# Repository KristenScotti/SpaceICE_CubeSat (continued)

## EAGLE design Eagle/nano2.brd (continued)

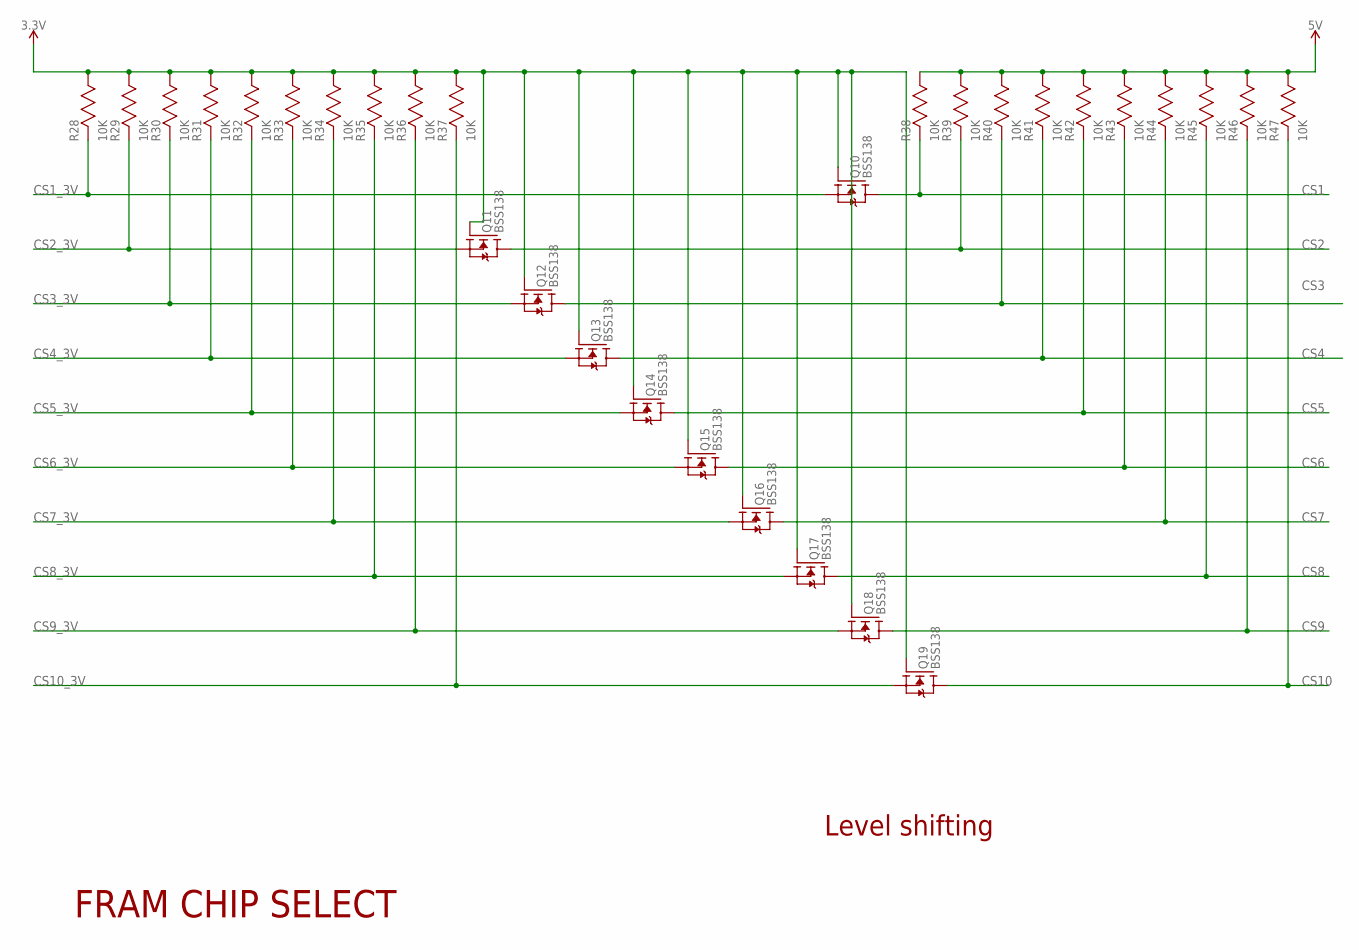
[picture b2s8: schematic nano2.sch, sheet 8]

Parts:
Q10, Q11, Q12, Q13, Q14, Q15, Q16, Q17, Q18, Q19: BSS138; SOT-23
R28, R29, R30, R31, R32, R33, R34, R35, R36, R37, R38, R39, R40, R41, R42, R43, R44, R45, R46, R47: 10K; RC0603N

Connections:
3.3V: Q10.G, Q11.G, Q12.G, Q13.G, Q14.G, Q15.G, Q16.G, Q17.G, Q18.G, Q19.G, R28.1 (11), R29.1 (11), R30.1 (11), R31.1 (11), R32.1 (11), R33.1 (11), R34.1 (11), R35.1 (11), R36.1 (11), R37.1 (11); also elsewhere on the board
5V: R38.1 (11), R39.1 (11), R40.1 (11), R41.1 (11), R42.1 (11), R43.1 (11), R44.1 (11), R45.1 (11), R46.1 (11), R47.1 (11); also elsewhere on the board
CS1: Q10.D, R38.2 (22); also elsewhere on the board
CS1_3V: Q10.S, R28.2 (22); also elsewhere on the board
CS2: Q11.D, R39.2 (22); also elsewhere on the board
CS2_3V: Q11.S, R29.2 (22); also elsewhere on the board
CS3: Q12.D, R40.2 (22); also elsewhere on the board
CS3_3V: Q12.S, R30.2 (22); also elsewhere on the board
CS4: Q13.D, R41.2 (22); also elsewhere on the board
CS4_3V: Q13.S, R31.2 (22); also elsewhere on the board
CS5: Q14.D, R42.2 (22); also elsewhere on the board
CS5_3V: Q14.S, R32.2 (22); also elsewhere on the board
CS6: Q15.D, R43.2 (22); also elsewhere on the board
CS6_3V: Q15.S, R33.2 (22); also elsewhere on the board
CS7: Q16.D, R44.2 (22); also elsewhere on the board
CS7_3V: Q16.S, R34.2 (22); also elsewhere on the board
CS8: Q17.D, R45.2 (22); also elsewhere on the board
CS8_3V: Q17.S, R35.2 (22); also elsewhere on the board
CS9: Q18.D, R46.2 (22); also elsewhere on the board
CS9_3V: Q18.S, R36.2 (22); also elsewhere on the board
CS10: Q19.D, R47.2 (22); also elsewhere on the board
CS10_3V: Q19.S, R37.2 (22); also elsewhere on the board

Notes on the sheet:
Level shifting
FRAM CHIP SELECT

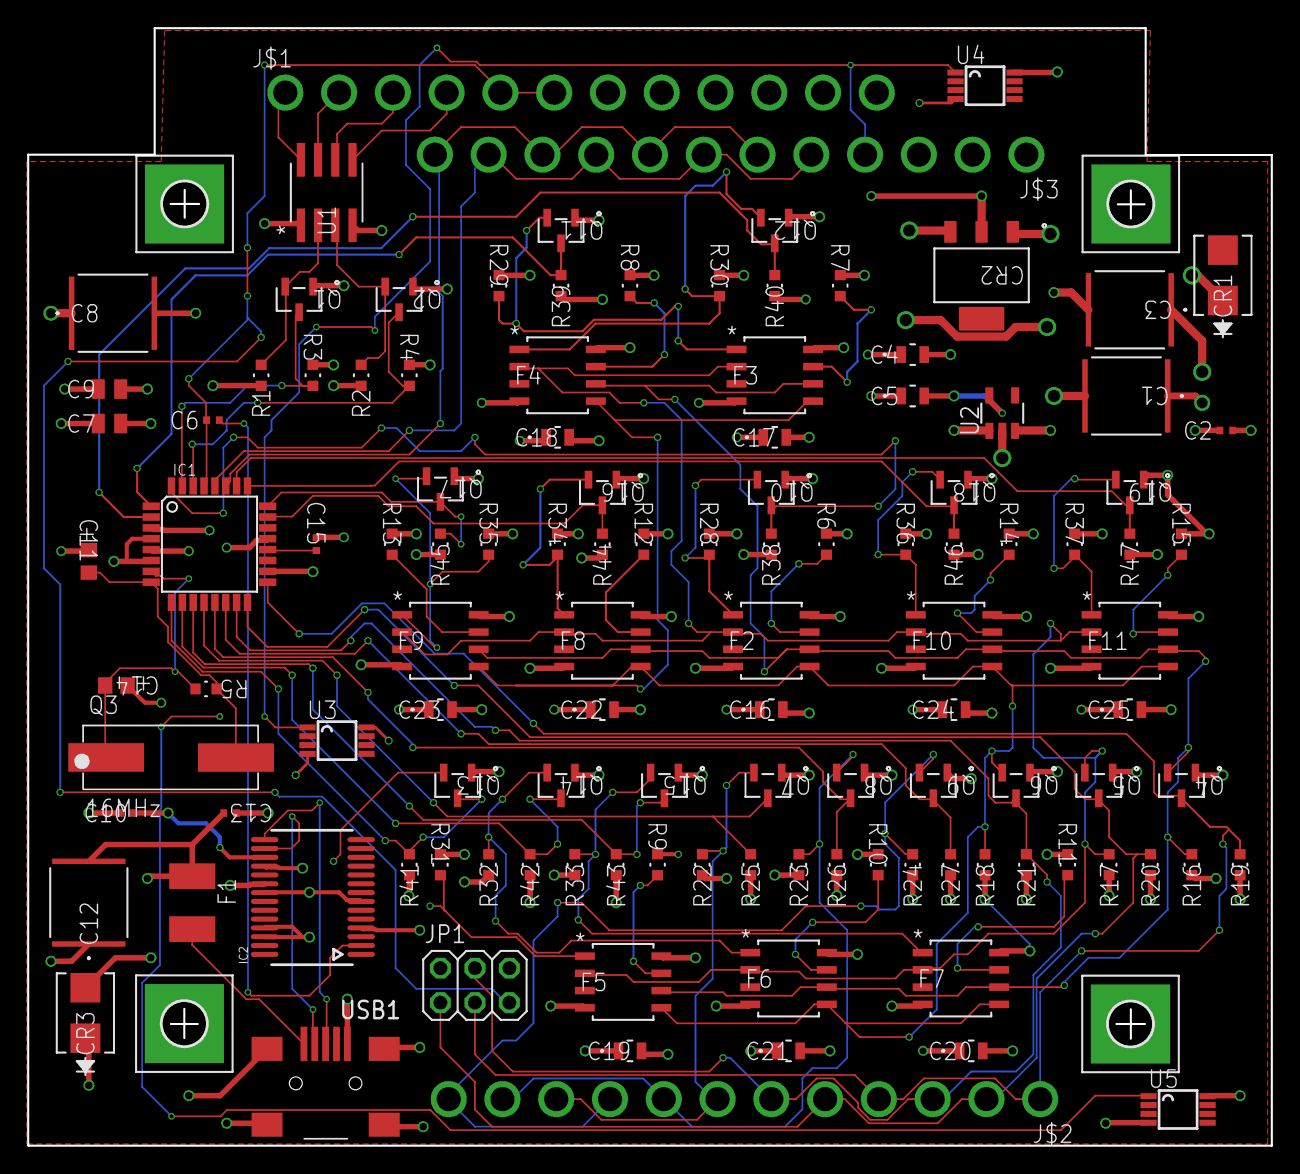
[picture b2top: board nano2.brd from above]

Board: 4 copper layers, 91.6 x 82.3 mm, 121 parts (0 on the bottom side), 66 nets.

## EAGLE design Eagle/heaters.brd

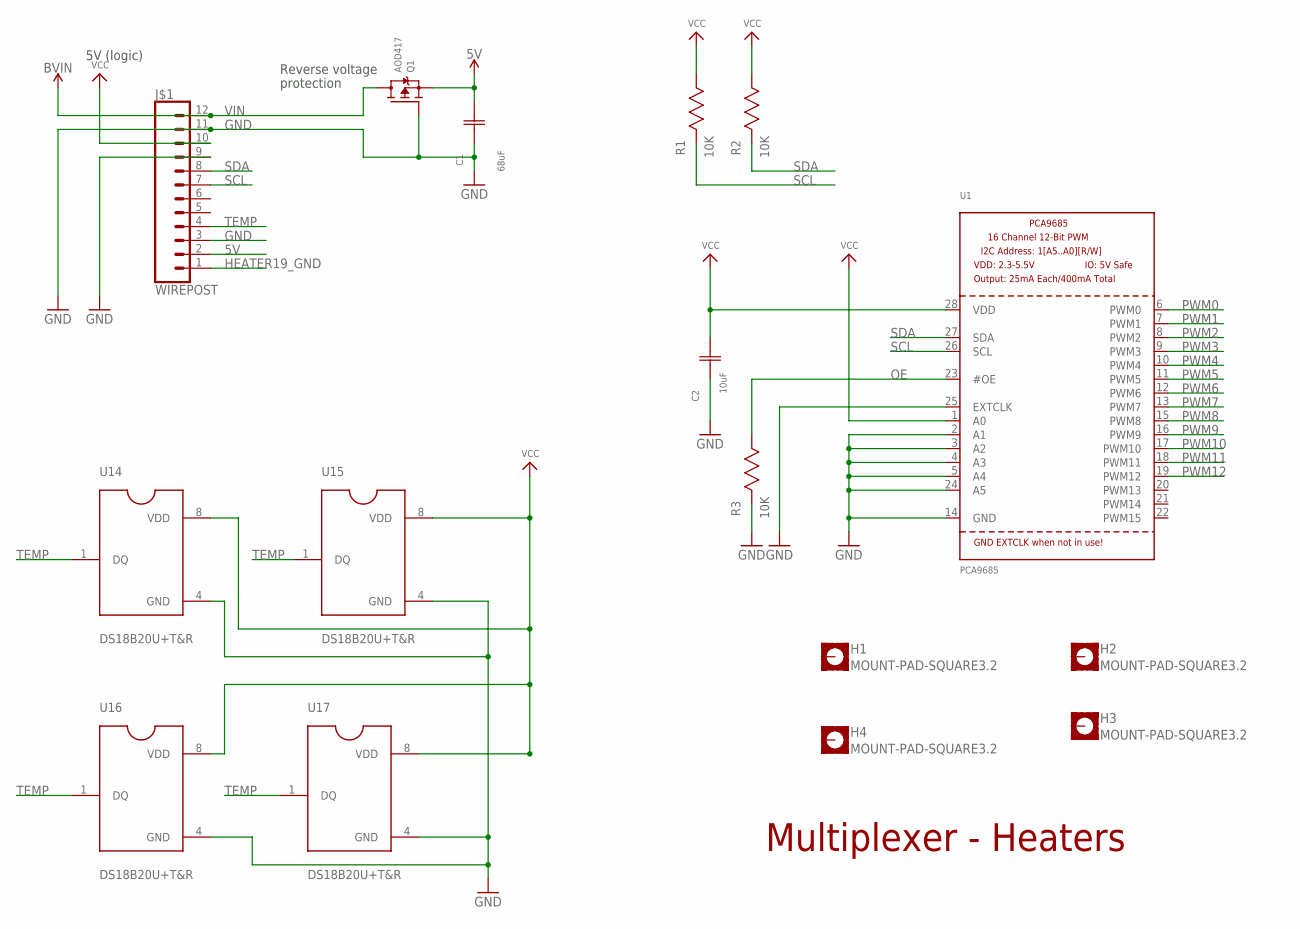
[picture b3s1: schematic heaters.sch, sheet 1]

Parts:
C1: 68uF; CAP_5750
C2: 10uF; 1206
H1, H2, H3, H4: MOUNT-PAD-SQUARE3.2; 3,2-PAD-SQUARE
J$1: WIREPOST; WIREWRAPPOST
Q1: AOD417; TO252
R1, R2, R3: 10K; RC0603N
U1: PCA9685; TSSOP28
U14, U15, U16, U17: DS18B20U+T&R; SOP65P500X110-8N

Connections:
5V: C1.2 (22), J$1.2, Q1.2 (S); also elsewhere on the board
GND: C1.1 (11), C2.1, J$1.3, J$1.9, J$1.11, Q1.1 (G), R3.2 (22), U1.2 (A1), U1.3 (A2), U1.4 (A3), U1.5 (A4), U1.14 (GND), U1.24 (A5), U1.25 (EXTCLK), U14.4 (GND), U15.4 (GND), U16.4 (GND), U17.4 (GND); also elsewhere on the board
HEATER19_GND: J$1.1
OE: R3.1 (11), U1.23 (#OE); also elsewhere on the board
PWM0: U1.6 (PWM0); also elsewhere on the board
PWM1: U1.7 (PWM1); also elsewhere on the board
PWM2: U1.8 (PWM2); also elsewhere on the board
PWM3: U1.9 (PWM3); also elsewhere on the board
PWM4: U1.10 (PWM4); also elsewhere on the board
PWM5: U1.11 (PWM5); also elsewhere on the board
PWM6: U1.12 (PWM6); also elsewhere on the board
PWM7: U1.13 (PWM7); also elsewhere on the board
PWM8: U1.15 (PWM8); also elsewhere on the board
PWM9: U1.16 (PWM9); also elsewhere on the board
PWM10: U1.17 (PWM10); also elsewhere on the board
PWM11: U1.18 (PWM11); also elsewhere on the board
PWM12: U1.19 (PWM12)
SCL: J$1.7, R1.2 (22), U1.26 (SCL); also elsewhere on the board
SDA: J$1.8, R2.2 (22), U1.27 (SDA); also elsewhere on the board
TEMP: J$1.4, U14.1 (DQ), U15.1 (DQ), U16.1 (DQ), U17.1 (DQ)
VCC: C2.2, J$1.10, R1.1 (11), R2.1 (11), U1.1 (A0), U1.28 (VDD), U14.8 (VDD), U15.8 (VDD), U16.8 (VDD), U17.8 (VDD); also elsewhere on the board
VIN: J$1.12, Q1.3 (D)

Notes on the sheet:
Reverse voltage
protection
5V (logic)
Multiplexer - Heaters

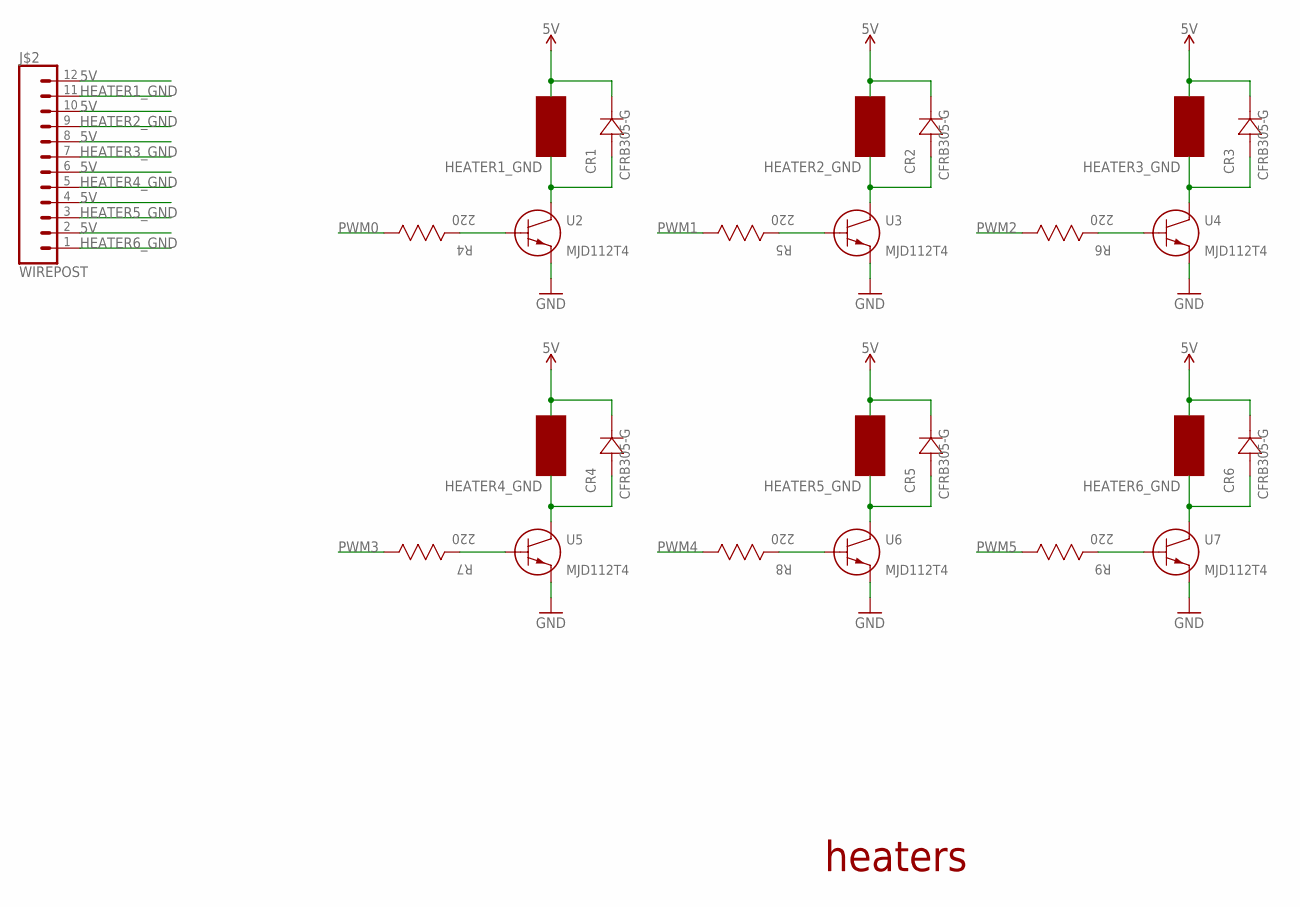
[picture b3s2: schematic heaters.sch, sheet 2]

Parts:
CR1, CR2, CR3, CR4, CR5, CR6: CFRB305-G; CFRB-G
J$2: WIREPOST; WIREWRAPPOST
R4, R5, R6, R7, R8, R9: 220; RC0603N
U2, U3, U4, U5, U6, U7: MJD112T4; DPAK

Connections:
5V: CR1.1 (2), CR2.1 (2), CR3.1 (2), CR4.1 (2), CR5.1 (2), CR6.1 (2), J$2.2, J$2.4, J$2.6, J$2.8, J$2.10, J$2.12; also elsewhere on the board
GND: U2.2 (E2), U3.2 (E2), U4.2 (E2), U5.2 (E2), U6.2 (E2), U7.2 (E2); also elsewhere on the board
HEATER1_GND: CR1.2 (1), J$2.11, U2.3 (C3)
HEATER2_GND: CR2.2 (1), J$2.9, U3.3 (C3)
HEATER3_GND: CR3.2 (1), J$2.7, U4.3 (C3)
HEATER4_GND: CR4.2 (1), J$2.5, U5.3 (C3)
HEATER5_GND: CR5.2 (1), J$2.3, U6.3 (C3)
HEATER6_GND: CR6.2 (1), J$2.1, U7.3 (C3)
unnamed: R5.2 (22), U3.1 (B1)
unnamed: R6.2 (22), U4.1 (B1)
unnamed: R7.2 (22), U5.1 (B1)
unnamed: R8.2 (22), U6.1 (B1)
unnamed: R9.2 (22), U7.1 (B1)
unnamed: R4.2 (22), U2.1 (B1)
PWM0: R4.1 (11); also elsewhere on the board
PWM1: R5.1 (11); also elsewhere on the board
PWM2: R6.1 (11); also elsewhere on the board
PWM3: R7.1 (11); also elsewhere on the board
PWM4: R8.1 (11); also elsewhere on the board
PWM5: R9.1 (11); also elsewhere on the board

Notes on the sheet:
HEATER
heaters

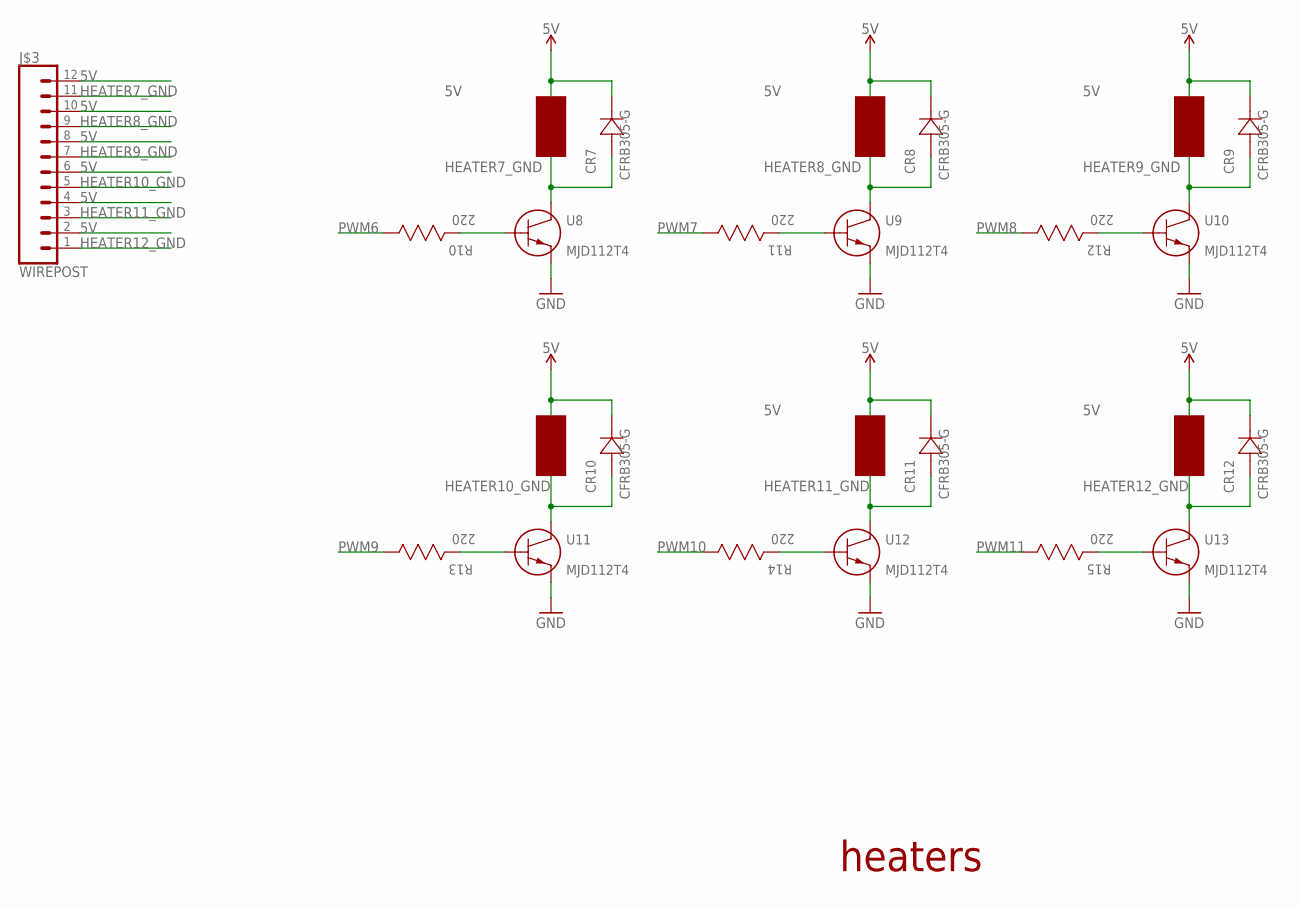
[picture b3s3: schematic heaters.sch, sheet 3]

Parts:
CR7, CR8, CR9, CR10, CR11, CR12: CFRB305-G; CFRB-G
J$3: WIREPOST; WIREWRAPPOST
R10, R11, R12, R13, R14, R15: 220; RC0603N
U8, U9, U10, U11, U12, U13: MJD112T4; DPAK

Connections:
5V: CR7.1 (2), CR8.1 (2), CR9.1 (2), CR10.1 (2), CR11.1 (2), CR12.1 (2), J$3.2, J$3.4, J$3.6, J$3.8, J$3.10, J$3.12; also elsewhere on the board
GND: U8.2 (E2), U9.2 (E2), U10.2 (E2), U11.2 (E2), U12.2 (E2), U13.2 (E2); also elsewhere on the board
HEATER7_GND: CR7.2 (1), J$3.11, U8.3 (C3)
HEATER8_GND: CR8.2 (1), J$3.9, U9.3 (C3)
HEATER9_GND: CR9.2 (1), J$3.7, U10.3 (C3)
HEATER10_GND: CR10.2 (1), J$3.5, U11.3 (C3)
HEATER11_GND: CR11.2 (1), J$3.3, U12.3 (C3)
HEATER12_GND: CR12.2 (1), J$3.1, U13.3 (C3)
unnamed: R10.2 (22), U8.1 (B1)
unnamed: R11.2 (22), U9.1 (B1)
unnamed: R12.2 (22), U10.1 (B1)
unnamed: R13.2 (22), U11.1 (B1)
unnamed: R14.2 (22), U12.1 (B1)
unnamed: R15.2 (22), U13.1 (B1)
PWM6: R10.1 (11); also elsewhere on the board
PWM7: R11.1 (11); also elsewhere on the board
PWM8: R12.1 (11); also elsewhere on the board
PWM9: R13.1 (11); also elsewhere on the board
PWM10: R14.1 (11); also elsewhere on the board
PWM11: R15.1 (11); also elsewhere on the board

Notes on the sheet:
HEATER
heaters

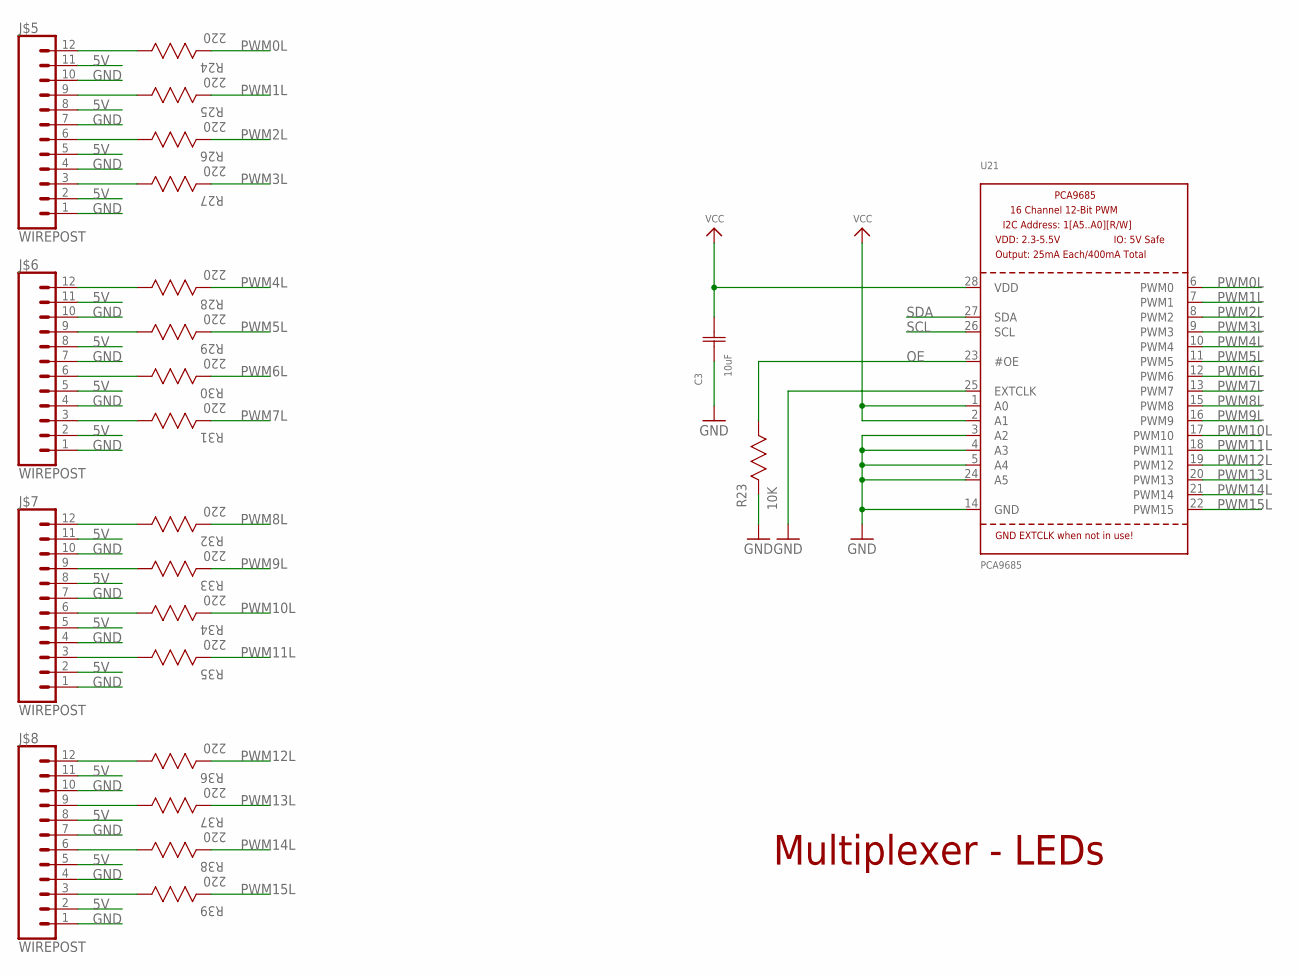
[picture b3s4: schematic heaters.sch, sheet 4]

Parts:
C3: 10uF; 1206
J$5, J$6, J$7, J$8: WIREPOST; WIREWRAPPOST
R23: 10K; RC0603N
R24, R25, R26, R27, R28, R29, R30, R31, R32, R33, R34, R35, R36, R37, R38, R39: 220; RC0603N
U21: PCA9685; TSSOP28

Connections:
5V: J$5.2, J$5.5, J$5.8, J$5.11, J$6.2, J$6.5, J$6.8, J$6.11, J$7.2, J$7.5, J$7.8, J$7.11, J$8.2, J$8.5, J$8.8, J$8.11; also elsewhere on the board
GND: C3.1, J$5.1, J$5.4, J$5.7, J$5.10, J$6.1, J$6.4, J$6.7, J$6.10, J$7.1, J$7.4, J$7.7, J$7.10, J$8.1, J$8.4, J$8.7, J$8.10, R23.2 (22), U21.3 (A2), U21.4 (A3), U21.5 (A4), U21.14 (GND), U21.24 (A5), U21.25 (EXTCLK); also elsewhere on the board
unnamed: J$5.12, R24.1 (11)
unnamed: J$5.9, R25.1 (11)
unnamed: J$5.6, R26.1 (11)
unnamed: J$5.3, R27.1 (11)
unnamed: J$6.12, R28.1 (11)
unnamed: J$6.9, R29.1 (11)
unnamed: J$6.6, R30.1 (11)
unnamed: J$6.3, R31.1 (11)
unnamed: J$7.12, R32.1 (11)
unnamed: J$7.9, R33.1 (11)
unnamed: J$7.6, R34.1 (11)
unnamed: J$7.3, R35.1 (11)
unnamed: J$8.12, R36.1 (11)
unnamed: J$8.9, R37.1 (11)
unnamed: J$8.6, R38.1 (11)
unnamed: J$8.3, R39.1 (11)
OE: R23.1 (11), U21.23 (#OE); also elsewhere on the board
PWM0L: R24.2 (22), U21.6 (PWM0)
PWM1L: R25.2 (22), U21.7 (PWM1)
PWM2L: R26.2 (22), U21.8 (PWM2)
PWM3L: R27.2 (22), U21.9 (PWM3)
PWM4L: R28.2 (22), U21.10 (PWM4)
PWM5L: R29.2 (22), U21.11 (PWM5)
PWM6L: R30.2 (22), U21.12 (PWM6)
PWM7L: R31.2 (22), U21.13 (PWM7)
PWM8L: R32.2 (22), U21.15 (PWM8)
PWM9L: R33.2 (22), U21.16 (PWM9)
PWM10L: R34.2 (22), U21.17 (PWM10)
PWM11L: R35.2 (22), U21.18 (PWM11)
PWM12L: R36.2 (22), U21.19 (PWM12)
PWM13L: R37.2 (22), U21.20 (PWM13)
PWM14L: R38.2 (22), U21.21 (PWM14)
PWM15L: R39.2 (22), U21.22 (PWM15)
SCL: U21.26 (SCL); also elsewhere on the board
SDA: U21.27 (SDA); also elsewhere on the board
VCC: C3.2, U21.1 (A0), U21.2 (A1), U21.28 (VDD); also elsewhere on the board

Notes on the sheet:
Multiplexer - LEDs

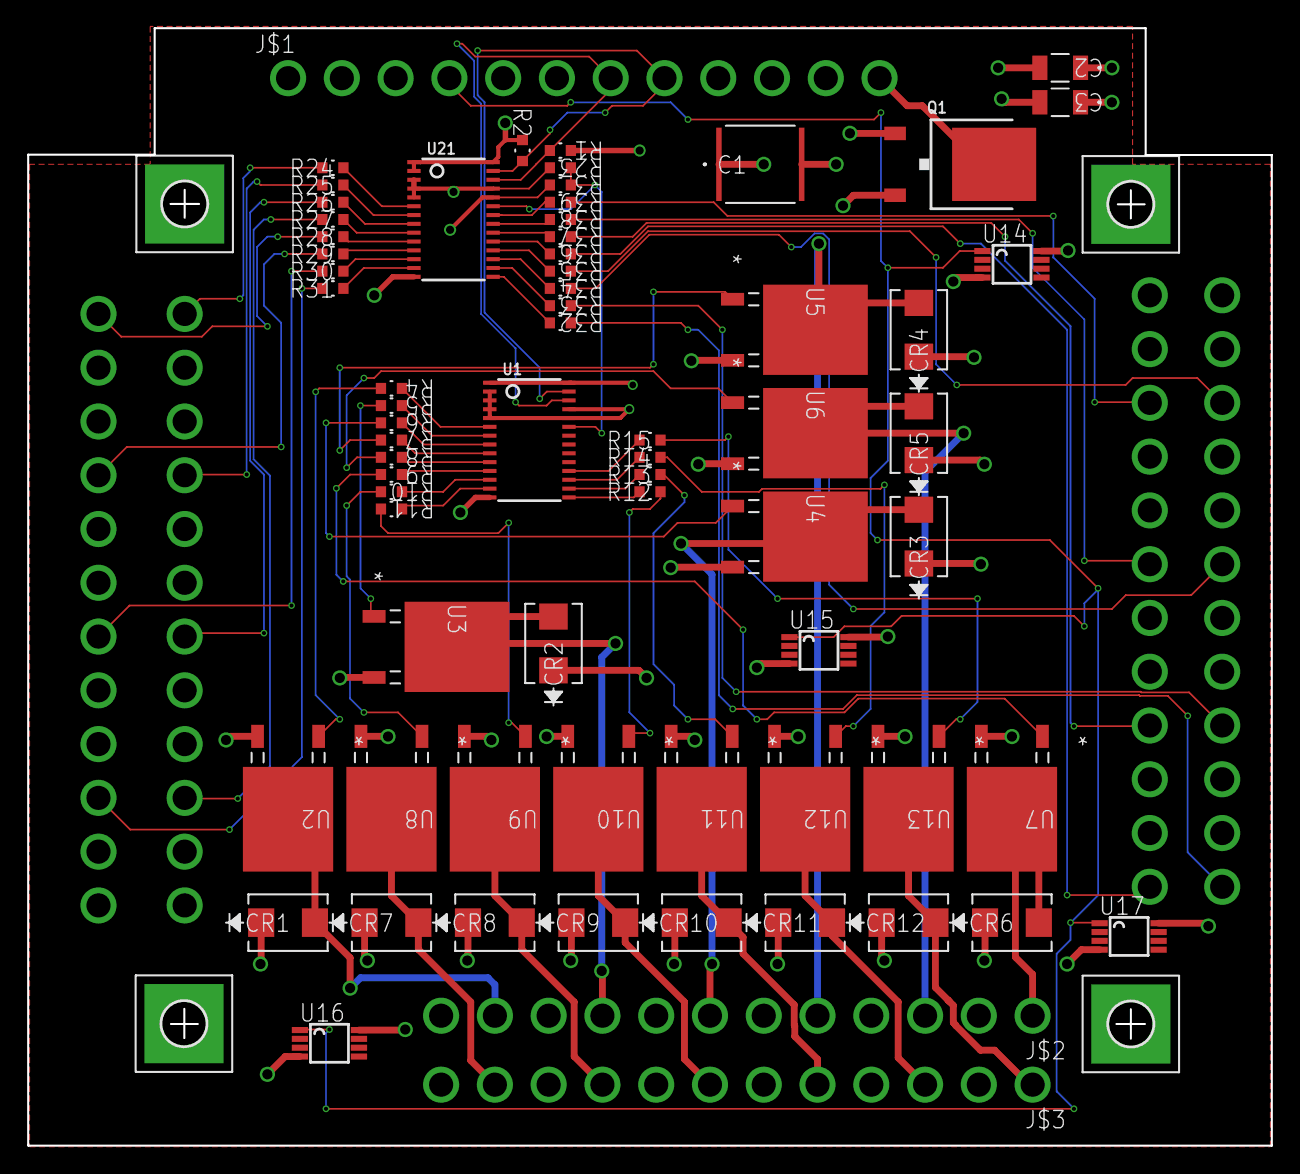
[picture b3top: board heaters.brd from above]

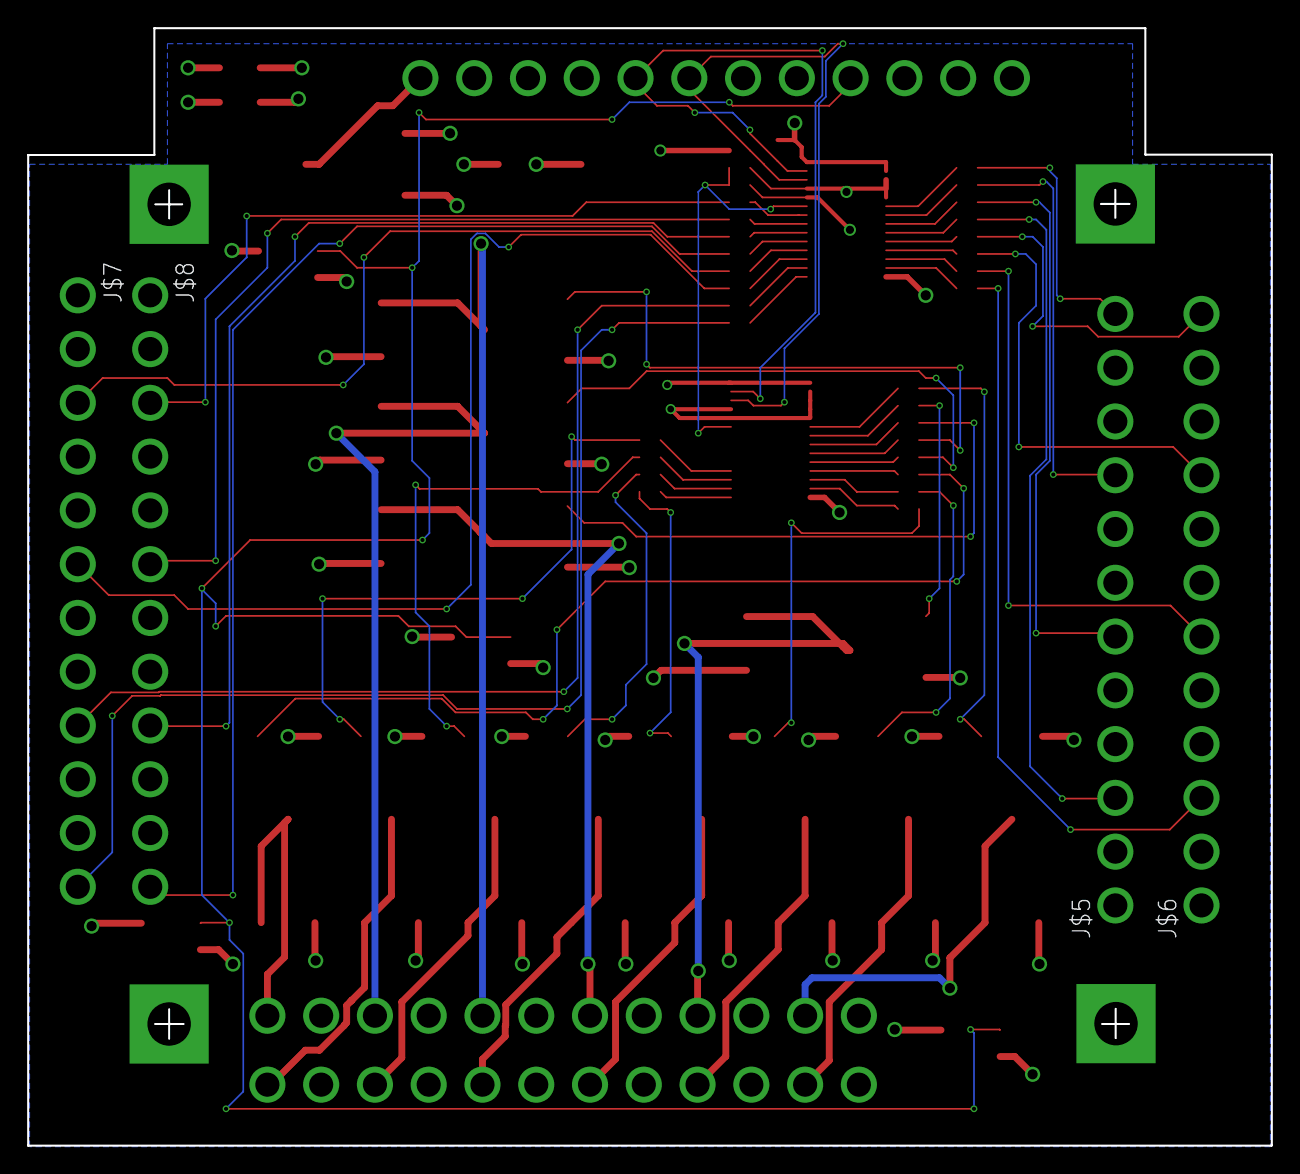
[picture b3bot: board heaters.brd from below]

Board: 4 copper layers, 91.6 x 82.3 mm, 77 parts (4 on the bottom side), 76 nets.

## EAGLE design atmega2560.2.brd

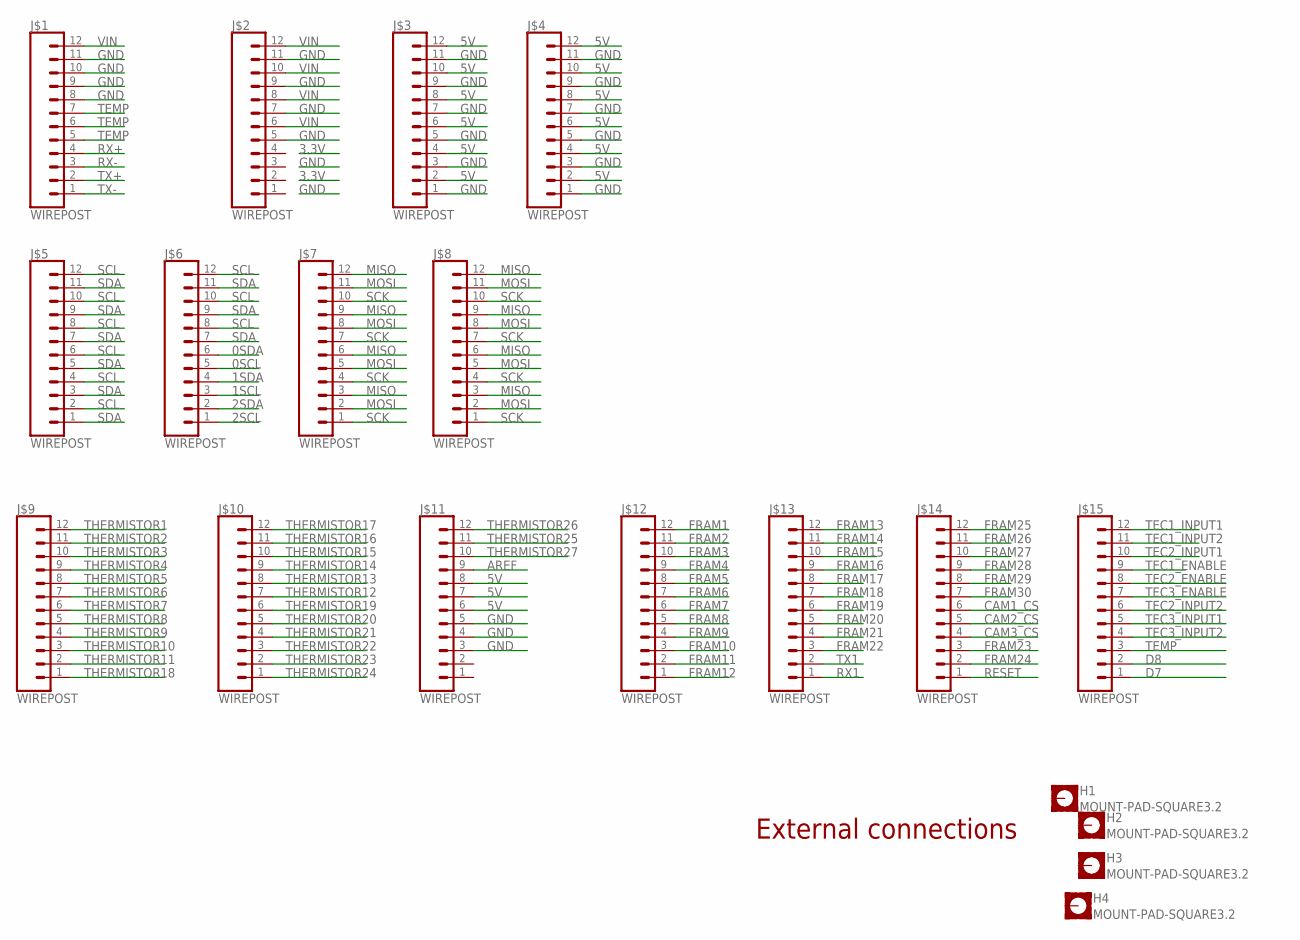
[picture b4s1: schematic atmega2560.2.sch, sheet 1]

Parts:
H1, H2, H3, H4: MOUNT-PAD-SQUARE3.2; 3,2-PAD-SQUARE
J$1, J$2, J$3, J$4, J$5, J$6, J$7, J$8, J$9, J$10, J$11, J$12, J$13, J$14, J$15: WIREPOST; WIREWRAPPOST

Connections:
0SCL: J$6.5; also elsewhere on the board
0SDA: J$6.6; also elsewhere on the board
1SCL: J$6.3; also elsewhere on the board
1SDA: J$6.4; also elsewhere on the board
2SCL: J$6.1; also elsewhere on the board
2SDA: J$6.2; also elsewhere on the board
5V: J$3.2, J$3.4, J$3.6, J$3.8, J$3.10, J$3.12, J$4.2, J$4.4, J$4.6, J$4.8, J$4.10, J$4.12, J$11.6, J$11.7, J$11.8; also elsewhere on the board
AREF: J$11.9; also elsewhere on the board
CAM1_CS: J$14.6; also elsewhere on the board
CAM2_CS: J$14.5; also elsewhere on the board
CAM3_CS: J$14.4; also elsewhere on the board
D7: J$15.1; also elsewhere on the board
D8: J$15.2; also elsewhere on the board
FRAM1: J$12.12; also elsewhere on the board
FRAM2: J$12.11; also elsewhere on the board
FRAM3: J$12.10; also elsewhere on the board
FRAM4: J$12.9; also elsewhere on the board
FRAM5: J$12.8; also elsewhere on the board
FRAM6: J$12.7; also elsewhere on the board
FRAM7: J$12.6; also elsewhere on the board
FRAM8: J$12.5; also elsewhere on the board
FRAM9: J$12.4; also elsewhere on the board
FRAM10: J$12.3; also elsewhere on the board
FRAM11: J$12.2; also elsewhere on the board
FRAM12: J$12.1; also elsewhere on the board
FRAM13: J$13.12; also elsewhere on the board
FRAM14: J$13.11; also elsewhere on the board
FRAM15: J$13.10; also elsewhere on the board
FRAM16: J$13.9; also elsewhere on the board
FRAM17: J$13.8; also elsewhere on the board
FRAM18: J$13.7; also elsewhere on the board
FRAM19: J$13.6; also elsewhere on the board
FRAM20: J$13.5; also elsewhere on the board
FRAM21: J$13.4; also elsewhere on the board
FRAM22: J$13.3; also elsewhere on the board
FRAM23: J$14.3; also elsewhere on the board
FRAM24: J$14.2; also elsewhere on the board
FRAM25: J$14.12; also elsewhere on the board
FRAM26: J$14.11; also elsewhere on the board
FRAM27: J$14.10; also elsewhere on the board
FRAM28: J$14.9; also elsewhere on the board
FRAM29: J$14.8; also elsewhere on the board
FRAM30: J$14.7; also elsewhere on the board
GND: J$1.8, J$1.9, J$1.10, J$1.11, J$2.5, J$2.7, J$2.9, J$2.11, J$3.1, J$3.3, J$3.5, J$3.7, J$3.9, J$3.11, J$4.1, J$4.3, J$4.5, J$4.7, J$4.9, J$4.11, J$11.3, J$11.4, J$11.5; also elsewhere on the board
MISO: J$7.3, J$7.6, J$7.9, J$7.12, J$8.3, J$8.6, J$8.9, J$8.12; also elsewhere on the board
MOSI: J$7.2, J$7.5, J$7.8, J$7.11, J$8.2, J$8.5, J$8.8, J$8.11; also elsewhere on the board
RESET: J$14.1; also elsewhere on the board
RX1: J$13.1; also elsewhere on the board
RX+: J$1.4; also elsewhere on the board
RX-: J$1.3; also elsewhere on the board
SCK: J$7.1, J$7.4, J$7.7, J$7.10, J$8.1, J$8.4, J$8.7, J$8.10; also elsewhere on the board
SCL: J$5.2, J$5.4, J$5.6, J$5.8, J$5.10, J$5.12, J$6.8, J$6.10, J$6.12; also elsewhere on the board
SDA: J$5.1, J$5.3, J$5.5, J$5.7, J$5.9, J$5.11, J$6.7, J$6.9, J$6.11; also elsewhere on the board
TEC1_ENABLE: J$15.9; also elsewhere on the board
TEC1_INPUT1: J$15.12; also elsewhere on the board
TEC1_INPUT2: J$15.11; also elsewhere on the board
TEC2_ENABLE: J$15.8; also elsewhere on the board
TEC2_INPUT1: J$15.10; also elsewhere on the board
TEC2_INPUT2: J$15.6; also elsewhere on the board
TEC3_ENABLE: J$15.7; also elsewhere on the board
TEC3_INPUT1: J$15.5; also elsewhere on the board
TEC3_INPUT2: J$15.4; also elsewhere on the board
TEMP: J$1.5, J$1.6, J$1.7, J$15.3; also elsewhere on the board
THERMISTOR1: J$9.12; also elsewhere on the board
THERMISTOR2: J$9.11; also elsewhere on the board
THERMISTOR3: J$9.10; also elsewhere on the board
THERMISTOR4: J$9.9; also elsewhere on the board
THERMISTOR5: J$9.8; also elsewhere on the board
THERMISTOR6: J$9.7; also elsewhere on the board
THERMISTOR7: J$9.6; also elsewhere on the board
THERMISTOR8: J$9.5; also elsewhere on the board
THERMISTOR9: J$9.4; also elsewhere on the board
THERMISTOR10: J$9.3; also elsewhere on the board
THERMISTOR11: J$9.2; also elsewhere on the board
THERMISTOR12: J$10.7; also elsewhere on the board
THERMISTOR13: J$10.8; also elsewhere on the board
THERMISTOR14: J$10.9; also elsewhere on the board
THERMISTOR15: J$10.10; also elsewhere on the board
THERMISTOR16: J$10.11; also elsewhere on the board
THERMISTOR17: J$10.12; also elsewhere on the board
THERMISTOR18: J$9.1; also elsewhere on the board
THERMISTOR19: J$10.6; also elsewhere on the board
THERMISTOR20: J$10.5; also elsewhere on the board
THERMISTOR21: J$10.4; also elsewhere on the board
THERMISTOR22: J$10.3; also elsewhere on the board
THERMISTOR23: J$10.2; also elsewhere on the board
THERMISTOR24: J$10.1; also elsewhere on the board
THERMISTOR25: J$11.11; also elsewhere on the board
THERMISTOR26: J$11.12; also elsewhere on the board
THERMISTOR27: J$11.10; also elsewhere on the board
TX1: J$13.2; also elsewhere on the board
TX+: J$1.2; also elsewhere on the board
TX-: J$1.1; also elsewhere on the board
VIN: J$1.12, J$2.6, J$2.8, J$2.10, J$2.12; also elsewhere on the board

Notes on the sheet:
External connections

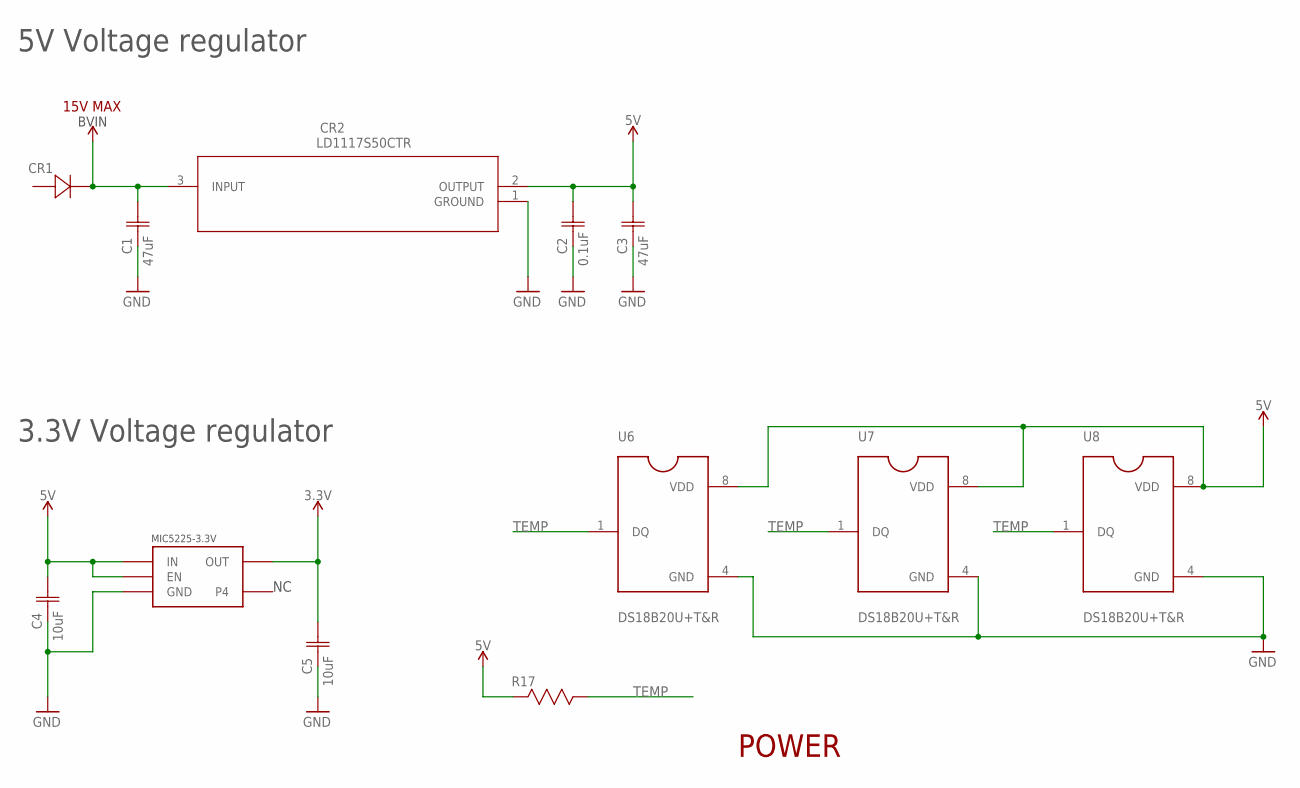
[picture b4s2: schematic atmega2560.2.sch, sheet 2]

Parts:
C1, C3: 47uF; CAP_5750
C2: 0.1uF; CAP_01
C4, C5: 10uF; CAP_GRM219R61A106KE44D
CR1: DIODE_600V_3A
CR2: LD1117S50CTR; SOT-223
R17: RES_4_7K; RC0603N
U1: MIC5225; SOT23-5
U6, U7, U8: DS18B20U+T&R; SOP65P500X110-8N

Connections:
3.3V: C5.2, U1.OUT; also elsewhere on the board
5V: C2.2, C3.2, C4.2, CR2.2 (OUTPUT), R17.2 (22), U1.EN, U1.IN, U6.8 (VDD), U7.8 (VDD), U8.8 (VDD); also elsewhere on the board
GND: C1.1, C2.1, C3.1, C4.1, C5.1, CR2.1 (GROUND), U1.GND, U6.4 (GND), U7.4 (GND), U8.4 (GND); also elsewhere on the board
TEMP: R17.1 (11), U6.1 (DQ), U7.1 (DQ), U8.1 (DQ); also elsewhere on the board
VIN: C1.2, CR1.1 (12), CR2.3 (INPUT); also elsewhere on the board

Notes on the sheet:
15V MAX
POWER
5V Voltage regulator
3.3V Voltage regulator

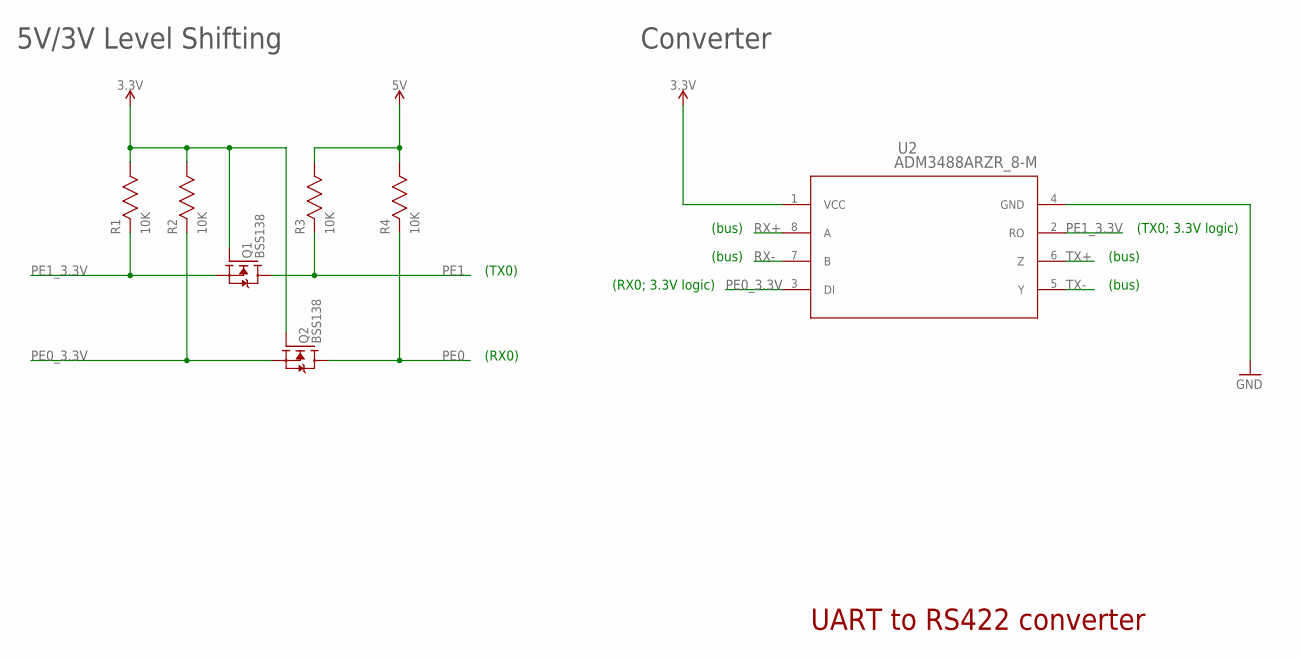
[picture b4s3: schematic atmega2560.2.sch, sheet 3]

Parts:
Q1, Q2: BSS138; SOT-23
R1, R2, R3, R4: 10K; RC0603N
U2: ADM3488ARZR_8-M; R_8-M

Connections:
3.3V: Q1.G, Q2.G, R1.1 (11), R2.1 (11), U2.1 (VCC); also elsewhere on the board
5V: R3.1 (11), R4.1 (11); also elsewhere on the board
GND: U2.4 (GND); also elsewhere on the board
PE0: Q2.D, R4.2 (22); also elsewhere on the board
PE0_3.3V: Q2.S, R2.2 (22), U2.3 (DI)
PE1: Q1.D, R3.2 (22); also elsewhere on the board
PE1_3.3V: Q1.S, R1.2 (22), U2.2 (RO)
RX+: U2.8 (A); also elsewhere on the board
RX-: U2.7 (B); also elsewhere on the board
TX+: U2.6 (Z); also elsewhere on the board
TX-: U2.5 (Y); also elsewhere on the board

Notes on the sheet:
5V/3V Level Shifting
UART to RS422 converter
(bus)
(RX0; 3.3V logic)
(TX0; 3.3V logic)
Converter
(RX0)
(TX0)
